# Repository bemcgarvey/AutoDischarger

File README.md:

# AutoDischarger 
 
A cell discharger/balancer for lipo batteries.  
PCB can be populated for 3S - 6S batteries.  
  
Operates in one of two modes: (push button switches modes)
1. Balance cells by discharging down to the lowest cell (starting mode) 
2. Storage mode - discharge all cells to 3.85V

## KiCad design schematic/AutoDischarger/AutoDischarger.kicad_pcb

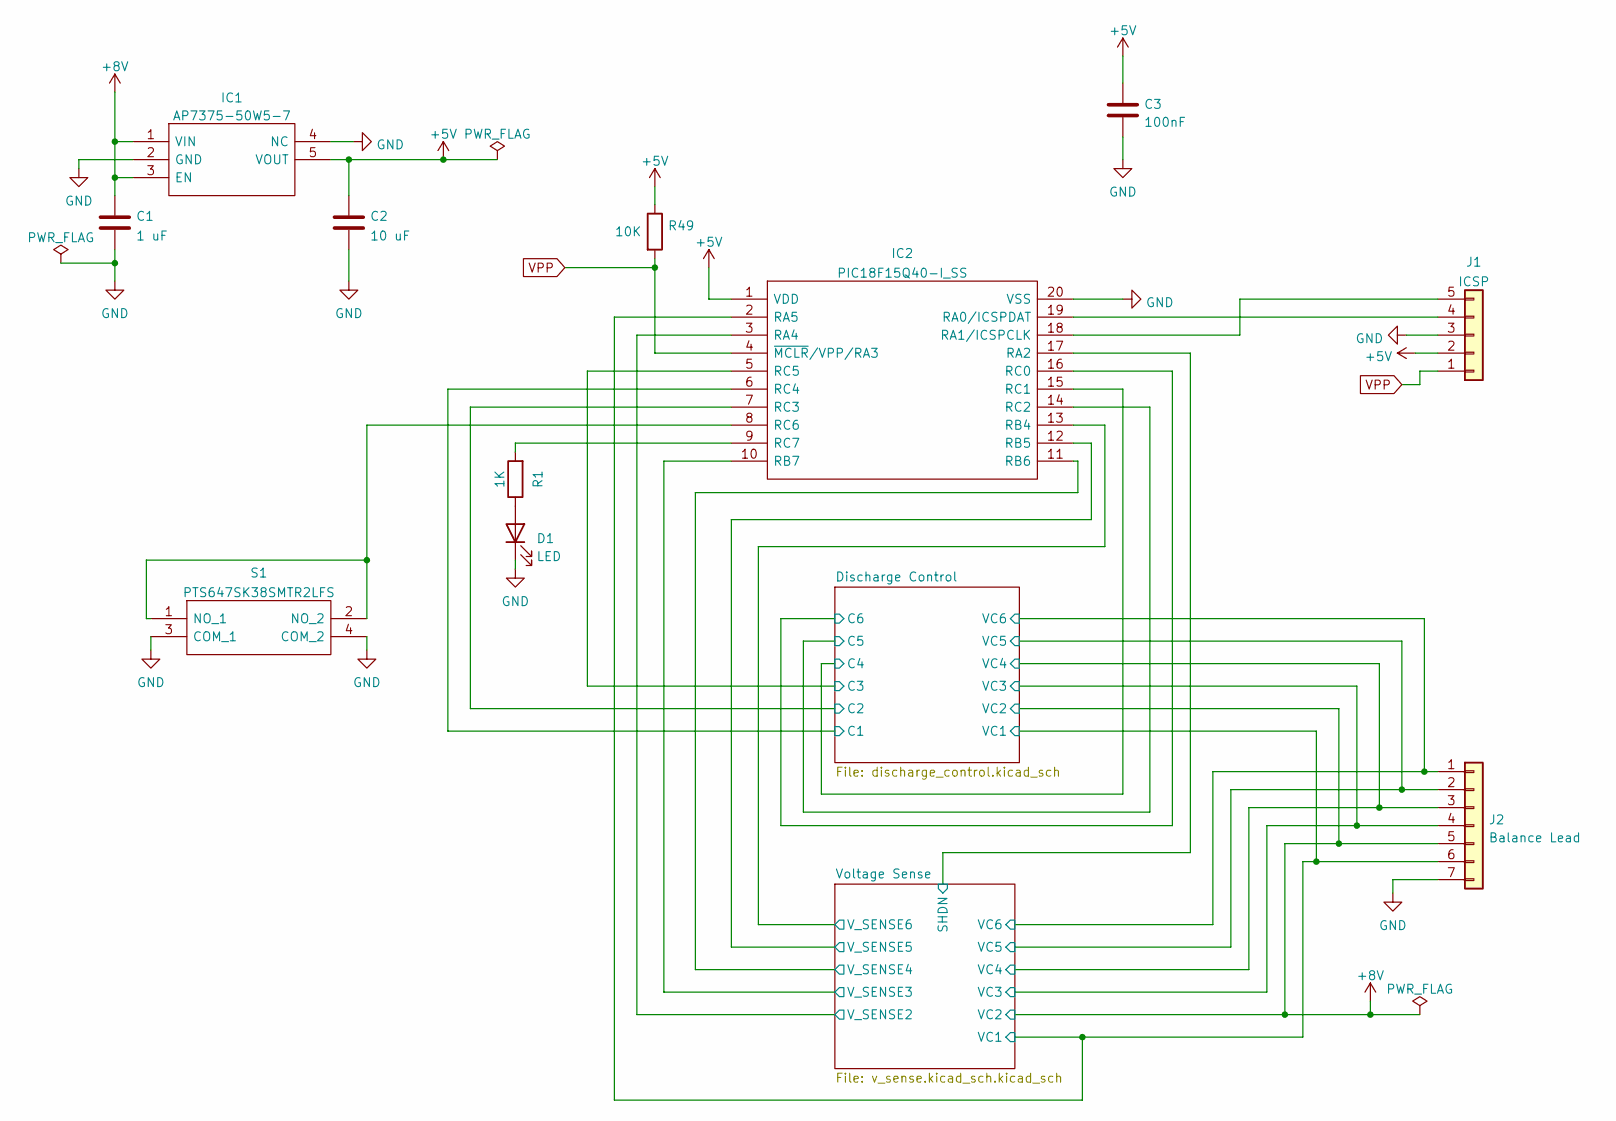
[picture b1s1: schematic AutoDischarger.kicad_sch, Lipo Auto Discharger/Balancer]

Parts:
C1: 1 uF; C_0603_1608Metric
C2: 10 uF; C_0603_1608Metric
C3: 100nF; C_0603_1608Metric
D1: LED; LED_0603_1608Metric
IC1: AP7375-50W5-7; SOT95P285X140-5N; Mouser Part Number 621-AP7375-50W5-7
IC2: PIC18F15Q40-I_SS; SOP65P780X200-20N; Mouser Part Number 579-PIC18F15Q40-I/SS
J1: ICSP; PinHeader_1x05_P2.54mm_Vertical
J2: Balance Lead; JST_XH_B7B-XH-A_1x07_P2.50mm_Vertical
R1: 1K; R_0603_1608Metric
R49: 10K; R_0603_1608Metric
S1: PTS647SK38SMTR2LFS; Mouser Part Number 611-PTS647SK38SMTR2L

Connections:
+5V: C2.1, C3.1, IC1.5 (VOUT), IC2.1 (VDD), J1.2, R49.1
+8V: C1.1, IC1.1 (VIN), IC1.3 (EN), J2.5; also elsewhere on the board
/Discharge Control/C1: IC2.6 (RC4); also elsewhere on the board
/Discharge Control/C2: IC2.7 (RC3); also elsewhere on the board
/Discharge Control/C3: IC2.5 (RC5); also elsewhere on the board
/Discharge Control/C4: IC2.15 (RC1); also elsewhere on the board
/Discharge Control/C5: IC2.14 (RC2); also elsewhere on the board
/Discharge Control/C6: IC2.16 (RC0); also elsewhere on the board
/Discharge Control/VC1: IC2.2 (RA5), J2.6; also elsewhere on the board
/Discharge Control/VC3: J2.4; also elsewhere on the board
/Discharge Control/VC4: J2.3; also elsewhere on the board
/Discharge Control/VC5: J2.2; also elsewhere on the board
/Discharge Control/VC6: J2.1; also elsewhere on the board
/Voltage Sense/SHDN: IC2.17 (RA2); also elsewhere on the board
/Voltage Sense/V_SENSE2: IC2.3 (RA4); also elsewhere on the board
/Voltage Sense/V_SENSE3: IC2.10 (RB7); also elsewhere on the board
/Voltage Sense/V_SENSE4: IC2.11 (RB6); also elsewhere on the board
/Voltage Sense/V_SENSE5: IC2.12 (RB5); also elsewhere on the board
/Voltage Sense/V_SENSE6: IC2.13 (RB4); also elsewhere on the board
GND: C1.2, C2.2, C3.2, D1.1 (K), IC1.2 (GND), IC1.4 (NC), IC2.20 (VSS), J1.3, J2.7, S1.3 (COM_1), S1.4 (COM_2); also elsewhere on the board
unnamed: D1.2 (A), R1.1
unnamed: IC2.8 (RC6), S1.1 (NO_1), S1.2 (NO_2)
unnamed: IC2.9 (RC7), R1.2
unnamed: IC2.18 (RA1/ICSPCLK), J1.5
unnamed: IC2.19 (RA0/ICSPDAT), J1.4
VPP: IC2.4 (~MCLR/VPP/RA3), J1.1, R49.2

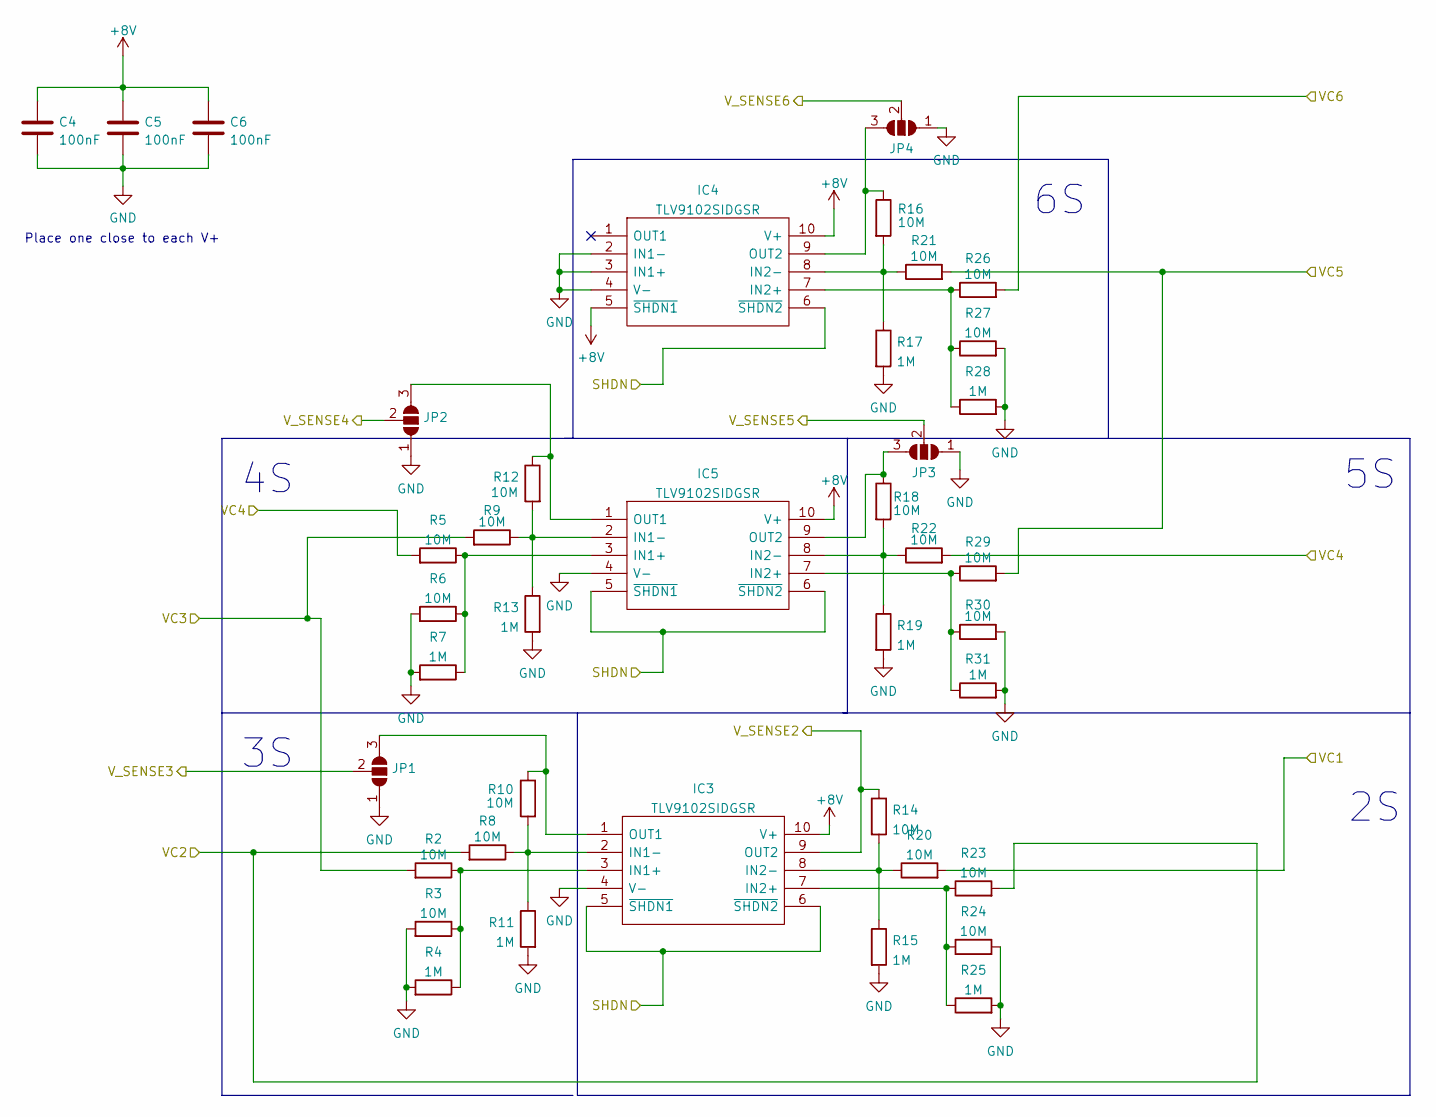
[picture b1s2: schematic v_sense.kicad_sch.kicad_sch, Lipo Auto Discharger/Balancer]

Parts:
C4, C5, C6: 100nF; C_0603_1608Metric
IC3, IC4, IC5: TLV9102SIDGSR; SOP50P490X110-10N; Mouser Part Number 595-TLV9102SIDGSR
JP1, JP2, JP3, JP4: SolderJumper_3_Open; SolderJumper-3_P1.3mm_Open_RoundedPad1.0x1.5mm_NumberLabels
R2, R3, R5, R6, R8, R9, R10, R12, R14, R16, R18, R20, R21, R22, R23, R24, R26, R27, R29, R30: 10M; R_0603_1608Metric
R4, R7, R11, R13, R15, R17, R19, R25, R28, R31: 1M; R_0603_1608Metric

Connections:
+8V: C4.1, C5.1, C6.1, IC3.10 (V+), IC4.5 (~SHDN1), IC4.10 (V+), IC5.10 (V+), R8.2, R23.2; also elsewhere on the board
/Discharge Control/VC1: R20.2; also elsewhere on the board
/Discharge Control/VC3: R2.2, R9.2; also elsewhere on the board
/Discharge Control/VC4: R5.2, R22.2; also elsewhere on the board
/Discharge Control/VC5: R21.2, R29.2; also elsewhere on the board
/Discharge Control/VC6: R26.2; also elsewhere on the board
/Voltage Sense/SHDN: IC3.5 (~SHDN1), IC3.6 (~SHDN2), IC4.6 (~SHDN2), IC5.5 (~SHDN1), IC5.6 (~SHDN2); also elsewhere on the board
/Voltage Sense/V_SENSE2: IC3.9 (OUT2), R14.1; also elsewhere on the board
/Voltage Sense/V_SENSE3: JP1.2 (C); also elsewhere on the board
/Voltage Sense/V_SENSE4: JP2.2 (C); also elsewhere on the board
/Voltage Sense/V_SENSE5: JP3.2 (C); also elsewhere on the board
/Voltage Sense/V_SENSE6: JP4.2 (C); also elsewhere on the board
GND: C4.2, C5.2, C6.2, IC3.4 (V-), IC4.2 (IN1-), IC4.3 (IN1+), IC4.4 (V-), IC5.4 (V-), JP1.1 (A), JP2.1 (A), JP3.1 (A), JP4.1 (A), R3.2, R4.2, R6.2, R7.2, R11.2, R13.2, R15.2, R17.2, R19.2, R24.2, R25.2, R27.2, R28.2, R30.2, R31.2; also elsewhere on the board
unnamed: IC3.1 (OUT1), JP1.3 (B), R10.1
unnamed: IC3.2 (IN1-), R8.1, R10.2, R11.1
unnamed: IC3.3 (IN1+), R2.1, R3.1, R4.1
unnamed: IC3.7 (IN2+), R23.1, R24.1, R25.1
unnamed: IC3.8 (IN2-), R14.2, R15.1, R20.1
unnamed: IC4.7 (IN2+), R26.1, R27.1, R28.1
unnamed: IC4.8 (IN2-), R16.2, R17.1, R21.1
unnamed: IC4.9 (OUT2), JP4.3 (B), R16.1
unnamed: IC5.1 (OUT1), JP2.3 (B), R12.1
unnamed: IC5.2 (IN1-), R9.1, R12.2, R13.1
unnamed: IC5.3 (IN1+), R5.1, R6.1, R7.1
unnamed: IC5.7 (IN2+), R29.1, R30.1, R31.1
unnamed: IC5.8 (IN2-), R18.2, R19.1, R22.1
unnamed: IC5.9 (OUT2), JP3.3 (B), R18.1

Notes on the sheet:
Place one close to each V+

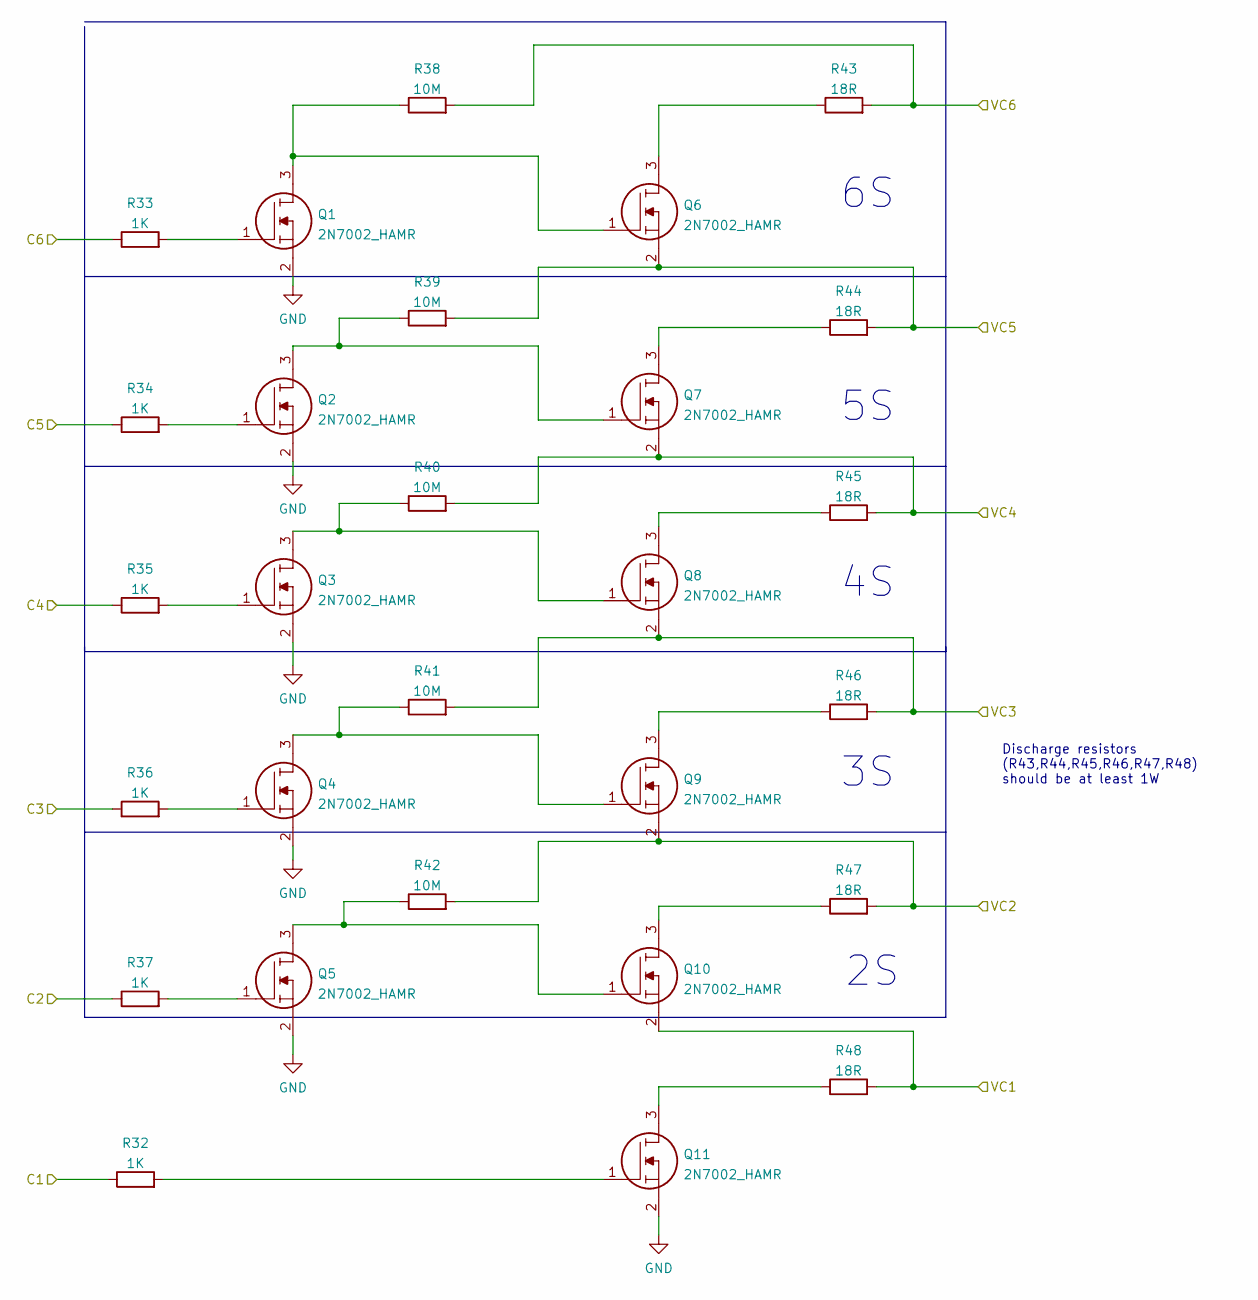
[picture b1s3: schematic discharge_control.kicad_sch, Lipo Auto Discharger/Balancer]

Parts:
Q1, Q2, Q3, Q4, Q5, Q6, Q7, Q8, Q9, Q10, Q11: 2N7002_HAMR; SOT-23; Mouser Part Number 771-2N7002/HAMR
R32, R33, R34, R35, R36, R37: 1K; R_0603_1608Metric
R38, R39, R40, R41, R42: 10M; R_0603_1608Metric
R43, R44, R45, R46, R47, R48: 18R; R_2512_6332Metric

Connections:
+8V: Q9.2, R42.2, R47.2; also elsewhere on the board
/Discharge Control/C1: R32.1; also elsewhere on the board
/Discharge Control/C2: R37.1; also elsewhere on the board
/Discharge Control/C3: R36.1; also elsewhere on the board
/Discharge Control/C4: R35.1; also elsewhere on the board
/Discharge Control/C5: R34.1; also elsewhere on the board
/Discharge Control/C6: R33.1; also elsewhere on the board
/Discharge Control/VC1: Q10.2, R48.2; also elsewhere on the board
/Discharge Control/VC3: Q8.2, R41.2, R46.2; also elsewhere on the board
/Discharge Control/VC4: Q7.2, R40.2, R45.2; also elsewhere on the board
/Discharge Control/VC5: Q6.2, R39.2, R44.2; also elsewhere on the board
/Discharge Control/VC6: R38.2, R43.2; also elsewhere on the board
GND: Q1.2, Q2.2, Q3.2, Q4.2, Q5.2, Q11.2; also elsewhere on the board
unnamed: Q1.1, R33.2
unnamed: Q1.3, Q6.1, R38.1
unnamed: Q2.1, R34.2
unnamed: Q2.3, Q7.1, R39.1
unnamed: Q3.1, R35.2
unnamed: Q3.3, Q8.1, R40.1
unnamed: Q4.1, R36.2
unnamed: Q4.3, Q9.1, R41.1
unnamed: Q5.1, R37.2
unnamed: Q6.3, R43.1
unnamed: Q7.3, R44.1
unnamed: Q8.3, R45.1
unnamed: Q9.3, R46.1
unnamed: Q5.3, Q10.1, R42.1
unnamed: Q10.3, R47.1
unnamed: Q11.1, R32.2
unnamed: Q11.3, R48.1

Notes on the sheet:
Discharge resistors (R43,R44,R45,R46,R47,R48) should be at least 1W

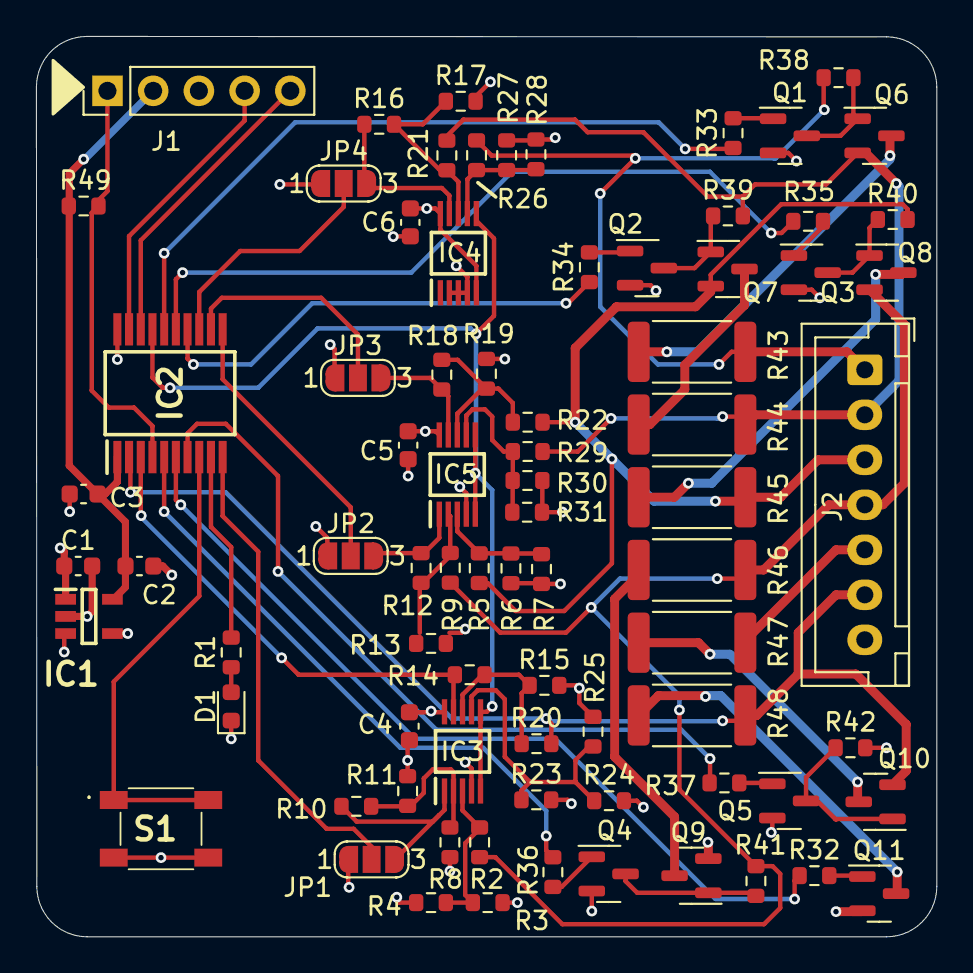
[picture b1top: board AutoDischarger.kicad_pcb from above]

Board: 4 copper layers, 50.0 x 50.0 mm, 79 parts (0 on the bottom side), 57 nets.

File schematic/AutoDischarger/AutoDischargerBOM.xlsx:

Source: | AutoDischarger
Component Count: | 78
Ref | Qnty | Value | Footprint
C1, | 1 | 1 uF | Capacitor_SMD:C_0603_1608Metric
C2, | 1 | 10 uF | Capacitor_SMD:C_0603_1608Metric
C3, C4, C5, C6, | 3 | 100nF | Capacitor_SMD:C_0603_1608Metric
D1, | 1 | LED | LED_SMD:LED_0603_1608Metric
IC1, | 1 | AP7375-50W5-7 | SOT95P285X140-5N
IC2, | 1 | PIC18F15Q40-I_SS | SamacSys_Parts:SOP65P780X200-20N
IC3, IC4, IC5, | 3 | TLV9102SIDGSR | SamacSys_Parts:SOP50P490X110-10N
J1, | 1 | ICSP | Connector_PinHeader_2.54mm:PinHeader_1x05_P2.54mm_Vertical
J2, | 1 | Balance Lead | Connector_JST:JST_XH_B7B-XH-A_1x07_P2.50mm_Vertical
JP1, JP2, JP3, JP4, | 4 | SolderJumper_3_Open | Jumper:SolderJumper-3_P1.3mm_Open_RoundedPad1.0x1.5mm_NumberLabels
Q1, Q2, Q3, Q4, Q5, Q6, Q7, Q8, Q9, Q10, Q11, | 11 | 2N7002_HAMR | Package_TO_SOT_SMD:SOT-23
R1, R32, R33, R34, R35, R36, R37, | 7 | 1K | Resistor_SMD:R_0603_1608Metric
R2, R3, R5, R6, R8, R9, R10, R12, R14, R16, R18, R20, R21, R22, R23, R24, R26, 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 | 25 | 10M | Resistor_SMD:R_0603_1608Metric
R4, R7, R11, R13, R15, R17, R19, R25, R28, R31, | 10 | 1M | Resistor_SMD:R_0603_1608Metric
R43, R44, R45, R46, R47, R48, | 6 | 120R | Resistor_SMD:R_1206_3216Metric
R49 | 1 | 10K | Resistor_SMD:R_0603_1608Metric
S1, | 1 | PTS647SK38SMTR2LFS | SamacSys_Parts:PTS647SK38SMTR2LFS

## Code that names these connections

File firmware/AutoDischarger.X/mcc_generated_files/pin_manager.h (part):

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#define RA0_SetHigh()            do { LATAbits.LATA0 = 1; } while(0)
#define RA0_SetLow()             do { LATAbits.LATA0 = 0; } while(0)
#define RA0_Toggle()             do { LATAbits.LATA0 = ~LATAbits.LATA0; } while(0)
#define RA0_GetValue()              PORTAbits.RA0
#define RA0_SetDigitalInput()    do { TRISAbits.TRISA0 = 1; } while(0)
#define RA0_SetDigitalOutput()   do { TRISAbits.TRISA0 = 0; } while(0)
#define RA0_SetPullup()             do { WPUAbits.WPUA0 = 1; } while(0)
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#define RA1_SetHigh()            do { LATAbits.LATA1 = 1; } while(0)
#define RA1_SetLow()             do { LATAbits.LATA1 = 0; } while(0)
#define RA1_Toggle()             do { LATAbits.LATA1 = ~LATAbits.LATA1; } while(0)
#define RA1_GetValue()              PORTAbits.RA1
#define RA1_SetDigitalInput()    do { TRISAbits.TRISA1 = 1; } while(0)
#define RA1_SetDigitalOutput()   do { TRISAbits.TRISA1 = 0; } while(0)
#define RA1_SetPullup()             do { WPUAbits.WPUA1 = 1; } while(0)
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// get/set SHDN aliases
#define SHDN_TRIS                 TRISAbits.TRISA2
#define SHDN_LAT                  LATAbits.LATA2
#define SHDN_PORT                 PORTAbits.RA2
#define SHDN_WPU                  WPUAbits.WPUA2
#define SHDN_OD                   ODCONAbits.ODCA2
#define SHDN_ANS                  ANSELAbits.ANSELA2
#define SHDN_SetHigh()            do { LATAbits.LATA2 = 1; } while(0)
#define SHDN_SetLow()             do { LATAbits.LATA2 = 0; } while(0)
#define SHDN_Toggle()             do { LATAbits.LATA2 = ~LATAbits.LATA2; } while(0)
#define SHDN_GetValue()           PORTAbits.RA2
#define SHDN_SetDigitalInput()    do { TRISAbits.TRISA2 = 1; } while(0)
#define SHDN_SetDigitalOutput()   do { TRISAbits.TRISA2 = 0; } while(0)
#define SHDN_SetPullup()          do { WPUAbits.WPUA2 = 1; } while(0)
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// get/set VSense2 aliases
#define VSense2_TRIS                 TRISAbits.TRISA4
#define VSense2_LAT                  LATAbits.LATA4
#define VSense2_PORT                 PORTAbits.RA4
#define VSense2_WPU                  WPUAbits.WPUA4
#define VSense2_OD                   ODCONAbits.ODCA4
#define VSense2_ANS                  ANSELAbits.ANSELA4
#define VSense2_SetHigh()            do { LATAbits.LATA4 = 1; } while(0)
#define VSense2_SetLow()             do { LATAbits.LATA4 = 0; } while(0)
#define VSense2_Toggle()             do { LATAbits.LATA4 = ~LATAbits.LATA4; } while(0)
#define VSense2_GetValue()           PORTAbits.RA4
#define VSense2_SetDigitalInput()    do { TRISAbits.TRISA4 = 1; } while(0)
#define VSense2_SetDigitalOutput()   do { TRISAbits.TRISA4 = 0; } while(0)
#define VSense2_SetPullup()          do { WPUAbits.WPUA4 = 1; } while(0)
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// get/set VSense1 aliases
#define VSense1_TRIS                 TRISAbits.TRISA5
#define VSense1_LAT                  LATAbits.LATA5
#define VSense1_PORT                 PORTAbits.RA5
#define VSense1_WPU                  WPUAbits.WPUA5
#define VSense1_OD                   ODCONAbits.ODCA5
#define VSense1_ANS                  ANSELAbits.ANSELA5
#define VSense1_SetHigh()            do { LATAbits.LATA5 = 1; } while(0)
#define VSense1_SetLow()             do { LATAbits.LATA5 = 0; } while(0)
#define VSense1_Toggle()             do { LATAbits.LATA5 = ~LATAbits.LATA5; } while(0)
#define VSense1_GetValue()           PORTAbits.RA5
#define VSense1_SetDigitalInput()    do { TRISAbits.TRISA5 = 1; } while(0)
#define VSense1_SetDigitalOutput()   do { TRISAbits.TRISA5 = 0; } while(0)
#define VSense1_SetPullup()          do { WPUAbits.WPUA5 = 1; } while(0)
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// get/set VSense6 aliases
#define VSense6_TRIS                 TRISBbits.TRISB4
#define VSense6_LAT                  LATBbits.LATB4
#define VSense6_PORT                 PORTBbits.RB4
#define VSense6_WPU                  WPUBbits.WPUB4
#define VSense6_OD                   ODCONBbits.ODCB4
#define VSense6_ANS                  ANSELBbits.ANSELB4
#define VSense6_SetHigh()            do { LATBbits.LATB4 = 1; } while(0)
#define VSense6_SetLow()             do { LATBbits.LATB4 = 0; } while(0)
#define VSense6_Toggle()             do { LATBbits.LATB4 = ~LATBbits.LATB4; } while(0)
#define VSense6_GetValue()           PORTBbits.RB4
#define VSense6_SetDigitalInput()    do { TRISBbits.TRISB4 = 1; } while(0)
#define VSense6_SetDigitalOutput()   do { TRISBbits.TRISB4 = 0; } while(0)
#define VSense6_SetPullup()          do { WPUBbits.WPUB4 = 1; } while(0)
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// get/set VSense5 aliases
#define VSense5_TRIS                 TRISBbits.TRISB5
#define VSense5_LAT                  LATBbits.LATB5
#define VSense5_PORT                 PORTBbits.RB5
#define VSense5_WPU                  WPUBbits.WPUB5
#define VSense5_OD                   ODCONBbits.ODCB5
#define VSense5_ANS                  ANSELBbits.ANSELB5
#define VSense5_SetHigh()            do { LATBbits.LATB5 = 1; } while(0)
#define VSense5_SetLow()             do { LATBbits.LATB5 = 0; } while(0)
#define VSense5_Toggle()             do { LATBbits.LATB5 = ~LATBbits.LATB5; } while(0)
#define VSense5_GetValue()           PORTBbits.RB5
#define VSense5_SetDigitalInput()    do { TRISBbits.TRISB5 = 1; } while(0)
#define VSense5_SetDigitalOutput()   do { TRISBbits.TRISB5 = 0; } while(0)
#define VSense5_SetPullup()          do { WPUBbits.WPUB5 = 1; } while(0)
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// get/set VSense4 aliases
#define VSense4_TRIS                 TRISBbits.TRISB6
#define VSense4_LAT                  LATBbits.LATB6
#define VSense4_PORT                 PORTBbits.RB6
#define VSense4_WPU                  WPUBbits.WPUB6
#define VSense4_OD                   ODCONBbits.ODCB6
#define VSense4_ANS                  ANSELBbits.ANSELB6
#define VSense4_SetHigh()            do { LATBbits.LATB6 = 1; } while(0)
#define VSense4_SetLow()             do { LATBbits.LATB6 = 0; } while(0)
#define VSense4_Toggle()             do { LATBbits.LATB6 = ~LATBbits.LATB6; } while(0)
#define VSense4_GetValue()           PORTBbits.RB6
#define VSense4_SetDigitalInput()    do { TRISBbits.TRISB6 = 1; } while(0)
#define VSense4_SetDigitalOutput()   do { TRISBbits.TRISB6 = 0; } while(0)
#define VSense4_SetPullup()          do { WPUBbits.WPUB6 = 1; } while(0)
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// get/set VSense3 aliases
#define VSense3_TRIS                 TRISBbits.TRISB7
#define VSense3_LAT                  LATBbits.LATB7
#define VSense3_PORT                 PORTBbits.RB7
#define VSense3_WPU                  WPUBbits.WPUB7
#define VSense3_OD                   ODCONBbits.ODCB7
#define VSense3_ANS                  ANSELBbits.ANSELB7
#define VSense3_SetHigh()            do { LATBbits.LATB7 = 1; } while(0)
#define VSense3_SetLow()             do { LATBbits.LATB7 = 0; } while(0)
#define VSense3_Toggle()             do { LATBbits.LATB7 = ~LATBbits.LATB7; } while(0)
#define VSense3_GetValue()           PORTBbits.RB7
#define VSense3_SetDigitalInput()    do { TRISBbits.TRISB7 = 1; } while(0)
#define VSense3_SetDigitalOutput()   do { TRISBbits.TRISB7 = 0; } while(0)
#define VSense3_SetPullup()          do { WPUBbits.WPUB7 = 1; } while(0)
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// get/set C6 aliases
#define C6_TRIS                 TRISCbits.TRISC0
#define C6_LAT                  LATCbits.LATC0
#define C6_PORT                 PORTCbits.RC0
#define C6_WPU                  WPUCbits.WPUC0
#define C6_OD                   ODCONCbits.ODCC0
#define C6_ANS                  ANSELCbits.ANSELC0
#define C6_SetHigh()            do { LATCbits.LATC0 = 1; } while(0)
#define C6_SetLow()             do { LATCbits.LATC0 = 0; } while(0)
#define C6_Toggle()             do { LATCbits.LATC0 = ~LATCbits.LATC0; } while(0)
#define C6_GetValue()           PORTCbits.RC0
#define C6_SetDigitalInput()    do { TRISCbits.TRISC0 = 1; } while(0)
#define C6_SetDigitalOutput()   do { TRISCbits.TRISC0 = 0; } while(0)
#define C6_SetPullup()          do { WPUCbits.WPUC0 = 1; } while(0)
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// get/set C4 aliases
#define C4_TRIS                 TRISCbits.TRISC1
#define C4_LAT                  LATCbits.LATC1
#define C4_PORT                 PORTCbits.RC1
#define C4_WPU                  WPUCbits.WPUC1
#define C4_OD                   ODCONCbits.ODCC1
#define C4_ANS                  ANSELCbits.ANSELC1
#define C4_SetHigh()            do { LATCbits.LATC1 = 1; } while(0)
#define C4_SetLow()             do { LATCbits.LATC1 = 0; } while(0)
#define C4_Toggle()             do { LATCbits.LATC1 = ~LATCbits.LATC1; } while(0)
#define C4_GetValue()           PORTCbits.RC1
#define C4_SetDigitalInput()    do { TRISCbits.TRISC1 = 1; } while(0)
#define C4_SetDigitalOutput()   do { TRISCbits.TRISC1 = 0; } while(0)
#define C4_SetPullup()          do { WPUCbits.WPUC1 = 1; } while(0)
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// get/set C5 aliases
#define C5_TRIS                 TRISCbits.TRISC2
#define C5_LAT                  LATCbits.LATC2
#define C5_PORT                 PORTCbits.RC2
#define C5_WPU                  WPUCbits.WPUC2
#define C5_OD                   ODCONCbits.ODCC2
#define C5_ANS                  ANSELCbits.ANSELC2
#define C5_SetHigh()            do { LATCbits.LATC2 = 1; } while(0)
#define C5_SetLow()             do { LATCbits.LATC2 = 0; } while(0)
#define C5_Toggle()             do { LATCbits.LATC2 = ~LATCbits.LATC2; } while(0)
#define C5_GetValue()           PORTCbits.RC2
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
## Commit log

2022-11-06 Initial KiCad project
2022-11-06 Initial schematic
2022-11-07 Op-amp datasheet
2022-11-07 Some schematic fixes and assigned footprints.
2022-11-07 Some schematic and footprint fixes
2022-11-08 Initial pcb - parts placed
2022-11-22 Initial pcb layout
2022-11-26 Generated BOM
2022-11-26 PCB tweaks
2023-01-26 Changed 5V regulator
2023-01-26 Updated BOM and fixed some labels
2023-01-26 Added pullup to MCLR
2023-01-27 Minor pcb tweaks
2023-02-02 Generated gerbers
2023-02-06 Initial firmware project
2023-02-21 Initial MCC files
2023-02-24 Initial storage algorithm
2023-02-24 Improved storage mode
2023-02-24 Balance mode working
2023-02-25 Improved mode change
2023-02-25 Updated for 18R 1W 2512 resistors
2023-02-25 Added WDT and improved low power
2023-02-26 Some improvements and new gerbers
2023-02-28 Added bad cell check
2023-03-13 New gerbers V1.1
2023-04-23 Adjusted discharge duty cycle to 50%
    Keeps temperature reasonable

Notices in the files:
firmware/AutoDischarger.X/mcc_generated_files/pin_manager.h:
(c) 2018 Microchip Technology Inc. and its subsidiaries.
